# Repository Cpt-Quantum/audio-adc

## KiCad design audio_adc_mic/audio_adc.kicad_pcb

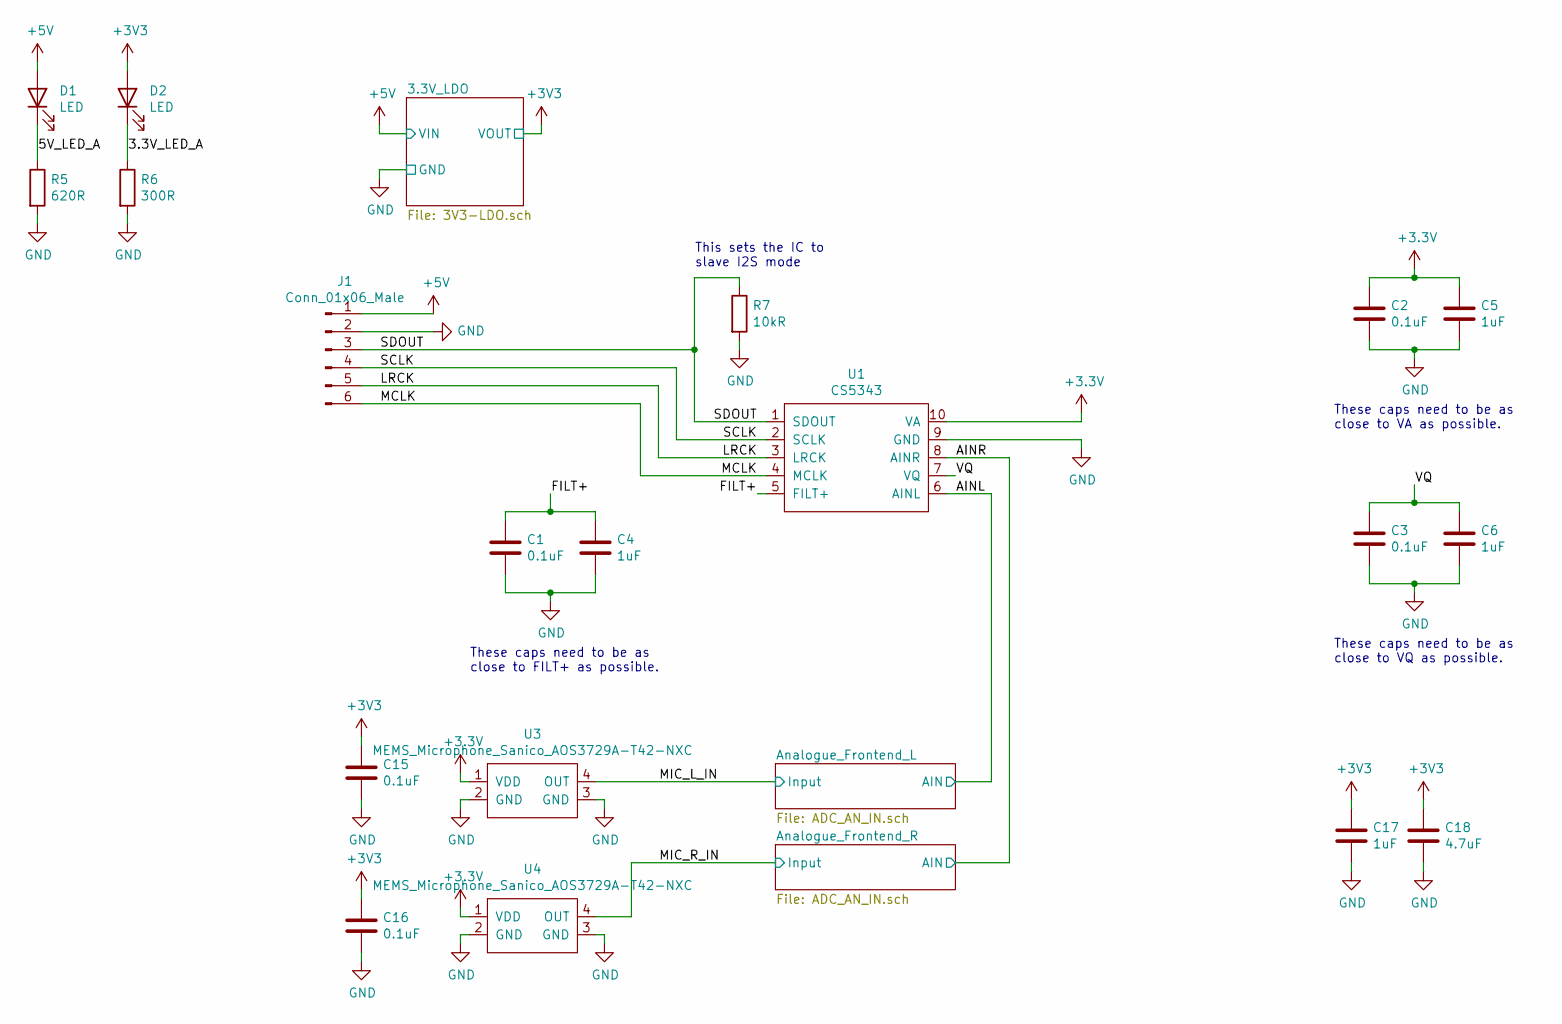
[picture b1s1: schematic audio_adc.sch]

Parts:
C1, C2, C3, C15, C16: 0.1uF; C_0603_1608Metric
C4, C5, C6, C17: 1uF; C_0603_1608Metric
C18: 4.7uF; C_0603_1608Metric
D1, D2: LED; LED_0603_1608Metric
J1: Conn_01x06_Male; PinHeader_1x06_P2.54mm_Vertical
R5: 620R; R_0603_1608Metric
R6: 300R; R_0603_1608Metric
R7: 10kR; R_0603_1608Metric
U1: CS5343; TSSOP-10_3x3mm_P0.5mm; Mfr Part # CS5343-CZZR
U3, U4: MEMS_Microphone_Sanico_AOS3729A-T42-NXC

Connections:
+3V3: C2.1, C5.1, C15.1, C16.1, C17.1, C18.1, D2.2 (A), U1.10 (VA), U3.1 (VDD), U4.1 (VDD); also elsewhere on the board
+5V: D1.2 (A), J1.1; also elsewhere on the board
/3.3V_LED_A: D2.1 (K), R6.1
/5V_LED_A: D1.1 (K), R5.1
/AINL: U1.6 (AINL); also elsewhere on the board
/AINR: U1.8 (AINR); also elsewhere on the board
/FILT+: C1.1, C4.1, U1.5 (FILT+)
/LRCK: J1.5, U1.3 (LRCK)
/MCLK: J1.6, U1.4 (MCLK)
/MIC_L_IN: U3.4 (OUT); also elsewhere on the board
/MIC_R_IN: U4.4 (OUT); also elsewhere on the board
/SCLK: J1.4, U1.2 (SCLK)
/SDOUT: J1.3, R7.1, U1.1 (SDOUT)
/VQ: C3.1, C6.1, U1.7 (VQ)
GND: C1.2, C2.2, C3.2, C4.2, C5.2, C6.2, C15.2, C16.2, C17.2, C18.2, J1.2, R5.2, R6.2, R7.2, U1.9 (GND), U3.2 (GND), U3.3 (GND), U4.2 (GND), U4.3 (GND); also elsewhere on the board

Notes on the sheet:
These caps need to be as close to VA as possible.
These caps need to be as close to VQ as possible.
These caps need to be as close to FILT+ as possible.
This sets the IC to slave I2S mode

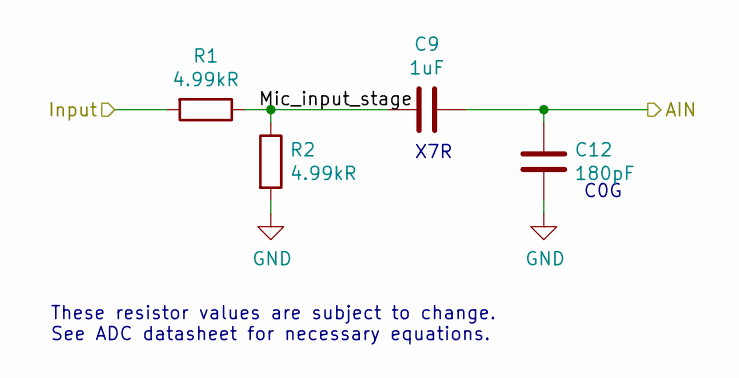
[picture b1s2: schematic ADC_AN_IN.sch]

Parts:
C10: 1uF; C_0603_1608Metric
C11: 180pF; C_0603_1608Metric
R3, R4: 4.99kR; R_0603_1608Metric

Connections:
/AINR: C10.2, C11.1; also elsewhere on the board
/Analogue_Frontend_R/Mic_input_stage: C10.1, R3.1, R4.1
/MIC_R_IN: R3.2; also elsewhere on the board
GND: C11.2, R4.2; also elsewhere on the board

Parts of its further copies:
C9: 1uF; C_0603_1608Metric
C12: 180pF; C_0603_1608Metric
R1, R2: 4.99kR; R_0603_1608Metric

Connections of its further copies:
/AINL: C9.2, C12.1; also elsewhere on the board
/Analogue_Frontend_L/Mic_input_stage: C9.1, R1.1, R2.1
/MIC_L_IN: R1.2; also elsewhere on the board
GND: C12.2, R2.2; also elsewhere on the board

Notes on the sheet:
These resistor values are subject to change. See ADC datasheet for necessary equations.
X7R
C0G

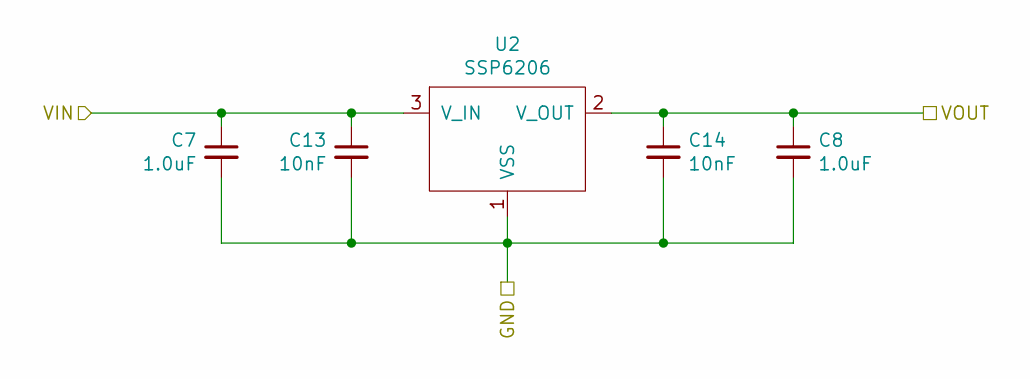
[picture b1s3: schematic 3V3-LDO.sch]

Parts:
C7, C8: 1.0uF; C_0603_1608Metric
C13, C14: 10nF; C_0603_1608Metric
U2: SSP6206; SOT-23; Mfr Part # SSP6206-33NR

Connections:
+3V3: C8.1, C14.1, U2.2 (V_OUT); also elsewhere on the board
+5V: C7.1, C13.1, U2.3 (V_IN); also elsewhere on the board
GND: C7.2, C8.2, C13.2, C14.2, U2.1 (VSS); also elsewhere on the board

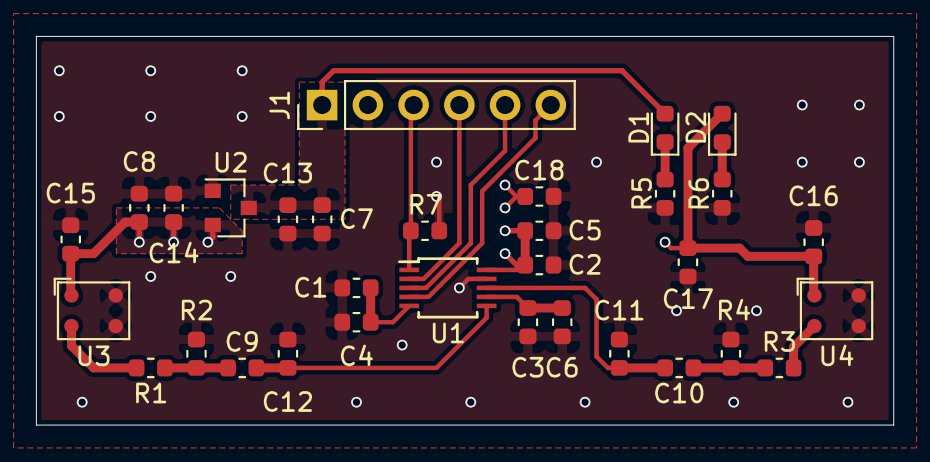
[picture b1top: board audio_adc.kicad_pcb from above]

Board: 2 copper layers, 47.6 x 21.6 mm, 32 parts (0 on the bottom side), 17 nets.

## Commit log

2020-09-09 Initial rev A files commit
2020-09-17 Added schematic pdf for microphone included board
2020-09-17 Added schematic pdf for the board with connectors
2020-09-17 Swapped the schematic pdf for microphone included board
